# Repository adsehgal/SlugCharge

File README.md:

# *SlugCharge*

SlugCharge was a student run project geared towards helping the homeless communit of Santa Cruz, CA. The project was led by four Electrical Engineering students at the University of California, Santa Cruz. The team aimed towards providing solar powered charging stations to the community so they can stay conencted with family and potential employers that may turn their life around! 

### My Roles

* PCB Design
* Mechnical Design
* Graphic Design
* Video Creation

<!-- START OF PCB SECTION -->
### PCB Design

#### PCB #1 - Testbench V1.0
[Project Files](https://github.com/adsehgal/SlugCharge/tree/master/SlugCharge_Testbench_V1.0) - KiCad
* We first started with making a testbench that was able to run our code and interact with the required I/O </br>
    Requirements:</br>
    * Utilize the **ATmega2560** as the main processor
    * Be **easliy programmable** for future code updates
    * Contain **visual annunciators** for easy state tracking 
    * Utilize **breakout pins** for off-board I/O control
    * Should **not require off-board voltage regulation**
    * Should be easily **hand assembled**
    * Restricted to a **2-layer PCB**
* The design was started off with referring to the Arduino Mega Development board and adapted to fit the required I/O:

* Next I moved onto laying out the PCB as per the requirements to get the following design:

</p>

#### PCB #2 - Motherboard V2.4
[Project Files](https://github.com/adsehgal/SlugCharge/tree/master/SlugCharge_Motherboard) - KiCad
* We followed the success of the testbench with a custom motherboard </br>
    Requirements:</br>
    * Utilize the **ATmega2560** as the main processor
    * Be **easliy programmable** for future code updates
    * Should **not require off-board voltage regulation**
    * Should **not be directly connected** to the individual lockers
    * Restricted to a **2-layer PCB**

To keep the motherboard physically isolated from the individual lockers, we decided to design a daughterboard for each locker that would connect to the motherboard via IDC cables

* Next I moved onto laying out the PCB as per the requirements to get the following design:

#### PCB #3 - Daughterboard V4.0
[Project Files](https://github.com/adsehgal/SlugCharge/tree/master/SlugCharge_Daughterboard) - KiCad
* We followed the success of the testbench with a custom daughterboard </br>
    Requirements:</br>
    * Connect with the motherboard **using IDC cables**
    * Provide a **voltage regulator per locker** to charge devices
    * Should be **easily replacable**
    * Should **not contain any complex devices**
    * Restricted to a **2-layer PCB**

To charge the devices in each locker, we decided to give each of these PCBs a second voltage regulator PCB for easy servicability. This regulator was chose to be the [TPS62133](https://github.com/adsehgal/SlugCharge/tree/master/TPS62133)

* Next I moved onto laying out the PCB as per the requirements to get the following design:

<!-- END OF PCB SECTION -->

<!--START OF  VOLTAGE REGULATOR -->
### Voltage Regulator selection

<!-- END OF VOLTAGE REGULATOR -->
[Regulator Comparison Sheet](https://github.com/adsehgal/SlugCharge/blob/master/Regulator_selection.pdf) - PDF</br>
[Regulator Design Files](https://github.com/adsehgal/SlugCharge/tree/master/TPS62133) - KiCad
* I decided to use the TPS62133 constant 5.0V switching regulator to charge connected devices. This regulator was selected for the following reasons:  </br>
  * Relatively low cost
  * Extremely high efficiency
  * Very low output ripple
  * On chip enable pin
  * High current capability
  
<!-- START OF MECH SECTION -->
### Mechanical Design
[Mechanical Drafts](https://github.com/adsehgal/SlugCharge/tree/master/Mechanical) - Fusion360
* Given the restrictions due to COVID-19, the team was unable to build the station, however we rendered a 3-D model for any future teams that may be intereste in taking up this project</br>
    Requirements:</br>
    * Be designed to accomodate the **average person height**
    * Hold at least **6 devices simultaneously**
    * Be resistant to **tampering**
    * **Solar Powered**

We drafted the 3-D model and orthographic drawings using Fusion360. This was done to aid future teams who may be interested in continuing this project

To educate the community how to use the station we developed two short instructional videos showing so. These can be downloaded via the following hyperlinks

* [Selecting a locker](https://github.com/adsehgal/SlugCharge/blob/master/Mechanical/Get_Device_Final.avi)
* [Retrieving your device](https://github.com/adsehgal/SlugCharge/blob/master/Mechanical/Select_Locker_FInal.avi)
<!-- END OF MECH SECTION -->

### Final Report
[The final team report can be found here](https://github.com/adsehgal/SlugCharge/blob/master/Final_report.pdf)

## Built With

* [KiCad](https://kicad-pcb.org/) - Used to design schematics and PCB layouts
* [Fusion 360](https://www.autodesk.com/products/fusion-360/overview) - Used to design mechanical drafts
* [Arduino IDE](https://www.arduino.cc/) - Used to code the charging station functionaility
* [Affinity Designer](http://affinity.serif.com/) - Used to design logos and other 2-D graphics
* [VSDC Video Editor](http://www.videosoftdev.com/) - Used to design education videos of the charging station

## Authors

* **Aditya Sehgal** - *Systems Integration lead, PCB Designer, Mechanical Drafter and Graphic Designer* - [AdSehgal](https://github.com/AdSehgal)

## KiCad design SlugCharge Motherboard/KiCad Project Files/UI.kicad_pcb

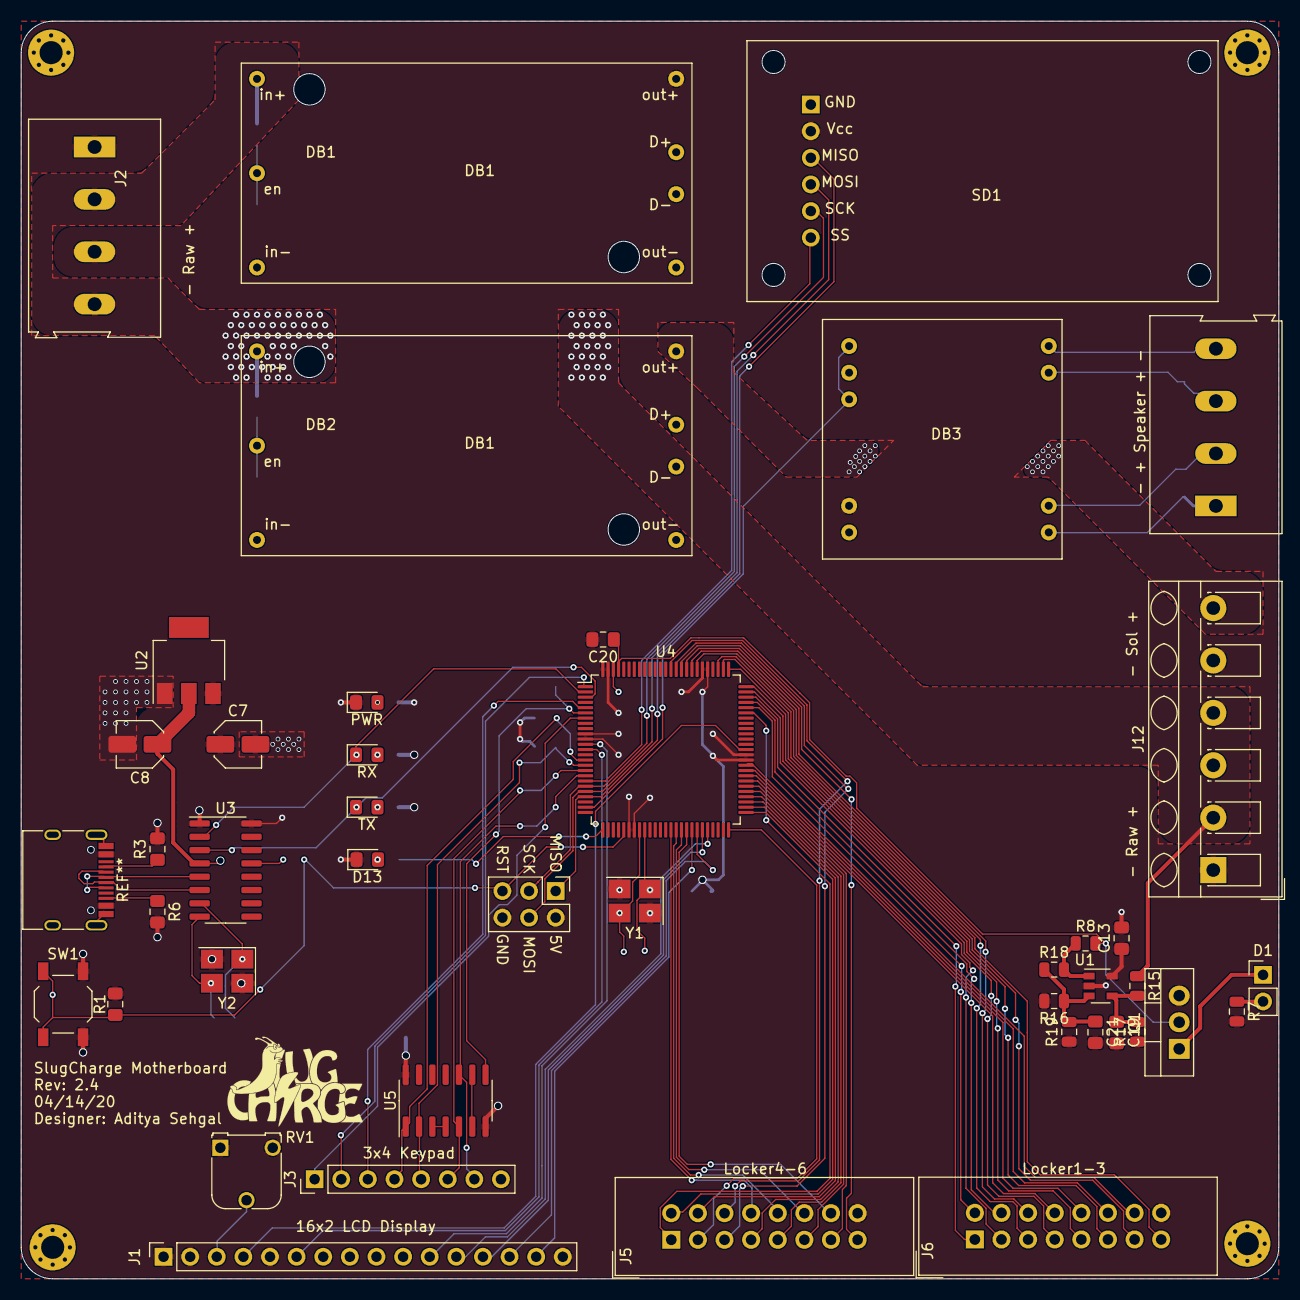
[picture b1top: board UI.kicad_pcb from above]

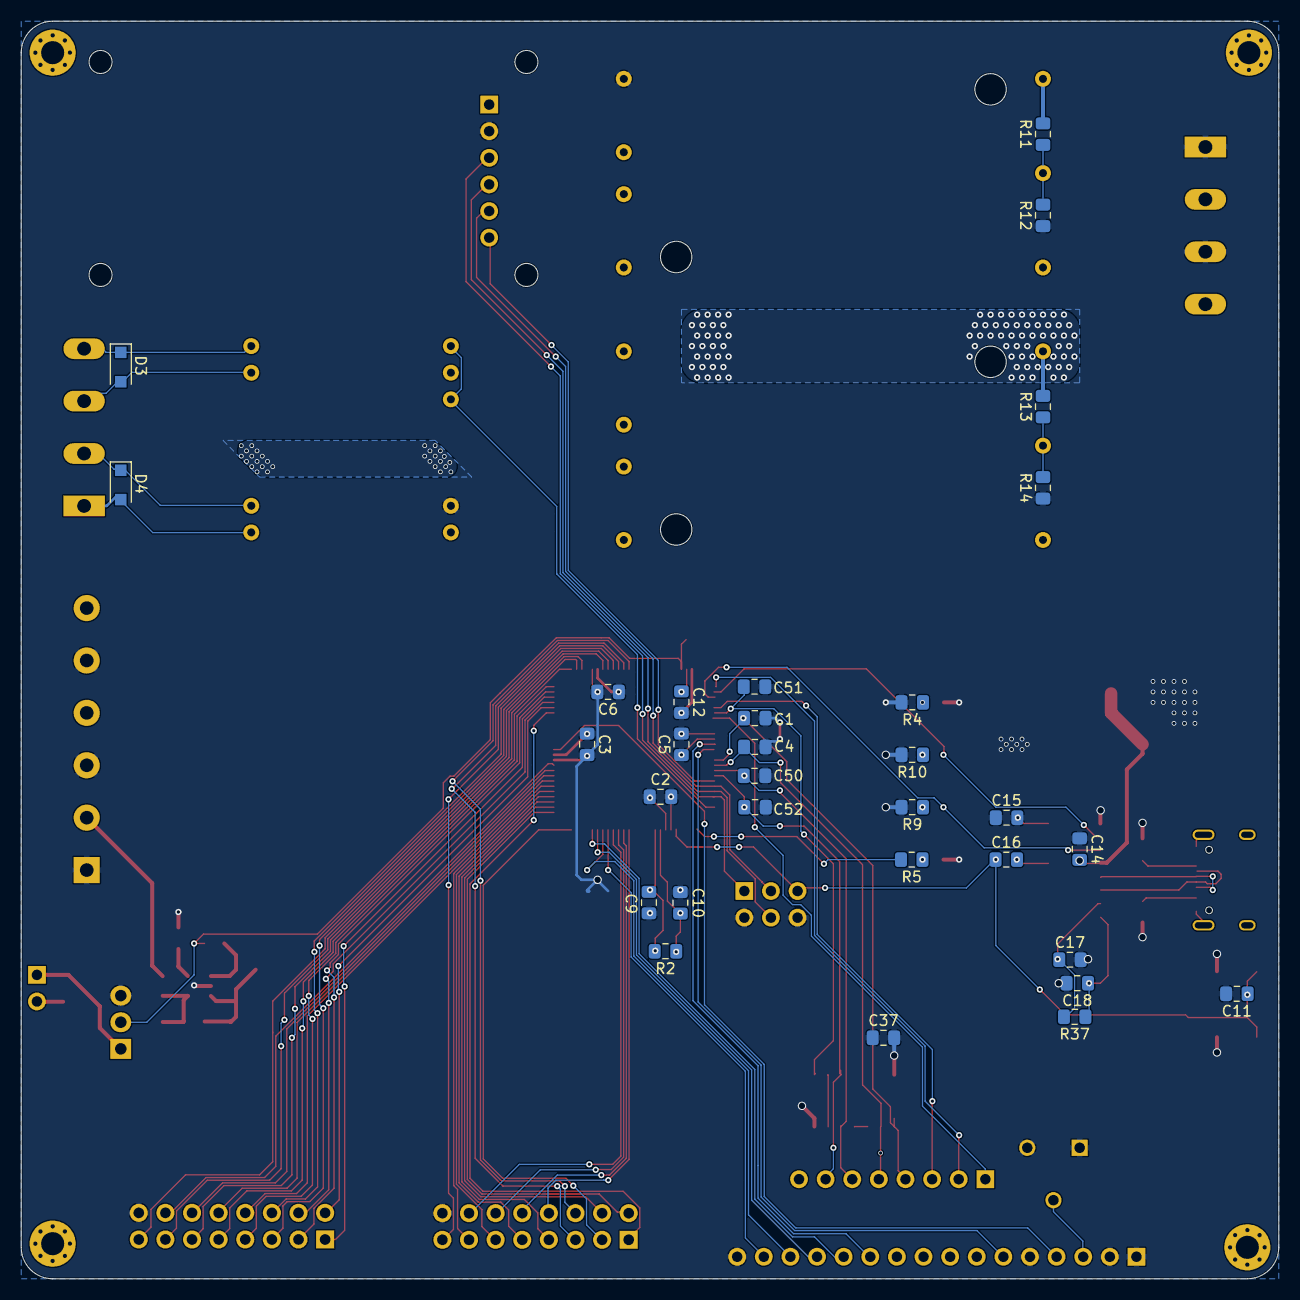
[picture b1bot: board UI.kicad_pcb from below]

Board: 2 copper layers, 120.0 x 120.0 mm, 80 parts (31 on the bottom side), 89 nets.

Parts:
C1, C2, C3, C4, C5, C6, C12, C13, C14, C15, C16, C19, C20, C21, C37, C50, C51, C52: 100nF; C_0805_2012Metric_Pad1.15x1.40mm_HandSolder
C7, C8: 10µF; C_Elec_4x5.4
C9, C10, C11, C17, C18: 22pF; C_0805_2012Metric_Pad1.15x1.40mm_HandSolder
D1: LED_Small; PinHeader_1x02_P2.54mm_Vertical
D3, D4: 1N4004; D_SOD-123F
D13: D13; LED_0805_2012Metric_Pad1.15x1.40mm_HandSolder
DB1: +5V_DB; LM2576_DB
DB2: +12V_DB; LM2576_DB
DB3: PAM8403_DB
H1, H2, H3, H4: MountingHole; MountingHole_2.2mm_M2_Pad_Via
J1: 16x2 LCD Display; PinSocket_1x16_P2.54mm_Vertical
J2: RAW in; TerminalBlock_Altech_AK300-4_P5.00mm
J3: 3x4 Keypad; PinHeader_1x08_P2.54mm_Vertical
J4: ICSP; PinHeader_2x03_P2.54mm_Vertical
J5: Locker4-6; IDC-Header_2x08_P2.54mm_Vertical
J6: Locker1-3; IDC-Header_2x08_P2.54mm_Vertical
J10: Speaker; TerminalBlock_Altech_AK300-4_P5.00mm
J12: Power; TerminalBlock_RND_205-00060_1x06_P5.00mm_45Degree
P1: USB_C_Plug; USB_C_SMD
PWR1: PWR; LED_0805_2012Metric_Pad1.15x1.40mm_HandSolder
Q1: IRF520; TO-220-3_Vertical
R1: 10KΩ; R_0805_2012Metric_Pad1.15x1.40mm_HandSolder
R2, R37: 1MΩ; R_0805_2012Metric_Pad1.15x1.40mm_HandSolder
R3, R6: 5K1; R_0805_2012Metric_Pad1.15x1.40mm_HandSolder
R4, R5, R9, R10: 330Ω; R_0805_2012Metric_Pad1.15x1.40mm_HandSolder
R7: 510R; R_0805_2012Metric
R8: 10K; R_0805_2012Metric
R11, R12, R13, R14: 0Ω; R_0805_2012Metric_Pad1.15x1.40mm_HandSolder
R15: 300K; R_0805_2012Metric
R16: 20K; R_0805_2012Metric
R17: 100K; R_0805_2012Metric
R18: 400K; R_0805_2012Metric
R19: 32.4K; R_0805_2012Metric
RV1: Cntrst Cntrl; Potentiometer_Runtron_RM-065_Vertical
RX1: RX; LED_0805_2012Metric_Pad1.15x1.40mm_HandSolder
SD1: microSD_Adapter; Micro_SD_Module
SW1: RST; SW_SPST_TL3342
TP1: TestPoint; logoinv
TX1: TX; LED_0805_2012Metric_Pad1.15x1.40mm_HandSolder
U1: TLV3201; SOT-23-5
U2: ams1117-3.3V; SOT-223
U3: CH340G; SOIC-16_3.9x9.9mm_P1.27mm
U4: ATmega2560-16AU; TQFP-100_14x14mm_P0.5mm
U5: 74HC08; SOIC-14_3.9x8.7mm_P1.27mm
Y1: 16MHz; Crystal_SMD_3225-4Pin_3.2x2.5mm_HandSoldering
Y2: 12MHz; Crystal_SMD_3225-4Pin_3.2x2.5mm_HandSoldering

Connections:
+3V3: C8.1, C14.2, U2.2 (VO), U3.4 (V3)
+5V: C1.2, C2.1, C2.2, C3.1, C3.2, C4.2, C5.1, C5.2, C6.1, C6.2, C7.1, C7.2, C8.2, C9.2, C10.2, C11.2, C12.2, C13.1, C13.2, C14.1, C15.1, C15.2, C17.2, C18.2, C19.2, C20.2, C21.2, C37.1, C37.2, C50.2, C51.2, C52.2, D13.1 (K), DB1.3 (out+), DB3.4 (Vcc), J1.1, J1.2, J1.5, J1.16, J2.1, J2.3, J4.2, J4.6, J5.16, J6.16, J12.1, J12.3, J12.5, P1.A4 (VBUS), P1.A9 (VBUS), P1.B4 (VBUS), P1.B9 (VBUS), PWR1.1 (K), Q1.3 (S), R1.2, R3.2, R4.2, R6.2, R7.2, R9.2, R10.2, R12.1, R14.1, R16.2, R17.1, R19.1, RV1.1, RV1.3, SD1.2 (Vcc), SW1.2, U1.2 (V-), U1.5 (V+), U2.1 (GND), U2.3 (VI), U3.1 (GND), U3.16 (VCC), U4.10 (VCC), U4.11 (GND), U4.31 (VCC), U4.32 (GND), U4.61 (VCC), U4.62 (GND), U4.80 (VCC), U4.81 (GND), U4.99 (GND), U4.100 (AVCC), U5.7 (GND), U5.14 (VCC), Y1.2, Y1.4, Y2.2, Y2.4
+12V: DB2.3 (out+), J12.6
+BATT: J2.2, J2.4, J12.2, J12.4, R11.2, R13.2, R15.1
+VSW: DB1.1 (in+), DB2.1 (in+)
/A10: J5.6, U4.87 (PK2)
/A11: J5.5, U4.86 (PK3)
/A12: J5.15, U4.85 (PK4)
/A13: J6.6, U4.84 (PK5)
/A14: J6.5, U4.83 (PK6)
/A15: J6.15, U4.82 (PK7)
/AREF: C12.1, U4.98 (AREF)
/BLI: C20.1, Q1.2 (G), R8.2, U4.97 (PF0)
/D2: C51.1, U4.6 (PE4), U5.8
/D3: J3.1, U4.7 (PE5)
/D4: J3.2, U4.1 (PG5)
/D5: J3.3, U4.5 (PE3)
/D6: C1.1, J3.4, U4.15 (PH3), U5.1
/D7: C4.1, J3.5, U4.16 (PH4), U5.2
/D8: C50.1, J3.6, U4.17 (PH5), U5.5
/D9: C52.1, J3.7, U4.18 (PH6), U5.10
/D11: DB3.1 (Lin), DB3.3 (Rin), U4.24 (PB5)
/D15: J1.4, U4.63 (PJ0)
/D16: J1.6, U4.13 (PH1)
/D17: J1.11, U4.12 (PH0)
/D18: J1.12, U4.46 (PD3)
/D19: J1.13, U4.45 (PD2)
/D20: J1.14, U4.44 (PD1)
/D21: J1.15, U4.43 (PD0)
/D22: J6.13, U4.78 (PA0)
/D23: J6.11, U4.77 (PA1)
/D24: J6.9, U4.76 (PA2)
/D25: J6.7, U4.75 (PA3)
/D26: J6.3, U4.74 (PA4)
/D27: J6.1, U4.73 (PA5)
/D28: J6.4, U4.72 (PA6)
/D29: J6.2, U4.71 (PA7)
/D30: J6.14, U4.60 (PC7)
/D31: J6.12, U4.59 (PC6)
/D32: J6.10, U4.58 (PC5)
/D33: J6.8, U4.57 (PC4)
/D34: J5.13, U4.56 (PC3)
/D35: J5.11, U4.55 (PC2)
/D36: J5.9, U4.54 (PC1)
/D37: J5.7, U4.53 (PC0)
/D38: J5.3, U4.50 (PD7)
/D39: J5.1, U4.70 (PG2)
/D40: J5.4, U4.52 (PG1)
/D41: J5.2, U4.51 (PG0)
/D42: J5.14, U4.42 (PL7)
/D43: J5.12, U4.41 (PL6)
/D44: J5.10, U4.40 (PL5)
/D45: J5.8, U4.39 (PL4)
/D50_MISO: J4.1, SD1.3 (MISO), U4.22 (PB3)
/D51_MOSI: J4.4, SD1.4 (MOSI), U4.21 (PB2)
/D52_SCK: J4.3, SD1.5 (SCK), U4.20 (PB1)
/D53_SS: SD1.6 (SS), U4.19 (PB0)
/D+: P1.A6 (D+), P1.B6 (D+)
/D-: P1.A7 (D-), P1.B7 (D-)
/OSC1: C9.1, R2.2, U4.34 (XTAL1), Y1.1
/OSC2: C10.1, R2.1, U4.33 (XTAL2), Y1.3
/RST: C11.1, C16.1, J4.5, R1.1, SW1.1, U4.30 (~RESET)
/RX: RX1.1 (K), U3.2 (TXD), U4.2 (PE0)
/TX: TX1.1 (K), U3.3 (RXD), U4.3 (PE1)
GNDREF: DB1.2 (in-), DB1.4 (out-), DB2.2 (in-), DB2.4 (out-), DB3.2 (CMN), DB3.5 (GND), P1.A1 (GND), P1.A12 (GND), P1.B1 (GND), P1.B12 (GND), P1.S1 (SHIELD), SD1.1 (GND)
unnamed: C16.2, U3.13 (~DTR)
unnamed: C17.1, R37.2, U3.7 (XI), Y2.1
unnamed: C18.1, R37.1, U3.8 (XO), Y2.3
unnamed: C19.1, R15.2, R17.2, U1.4 (-)
unnamed: C21.1, R16.1, R18.1, R19.2, U1.3 (+)
unnamed: D1.1 (K), Q1.1 (D)
unnamed: D1.2 (A), R7.1
unnamed: D3.1 (K), DB3.6 (Rout-), J10.4
unnamed: D3.2 (A), DB3.7 (Rout+), J10.3
unnamed: D4.1 (K), DB3.8 (Lout+), J10.2
unnamed: D4.2 (A), DB3.9 (Lout-), J10.1
unnamed: D13.2 (A), R5.1
unnamed: DB1.5 (en), R11.1, R12.2
unnamed: DB2.5 (en), R13.1, R14.2
unnamed: J1.3, RV1.2
unnamed: P1.A5 (CC1), R3.1
unnamed: P1.B5 (CC2), R6.1
unnamed: PWR1.2 (A), R4.1
unnamed: R5.2, U4.26 (PB7)
unnamed: R9.1, TX1.2 (A)
unnamed: R10.1, RX1.2 (A)
unnamed: R8.1, R18.2, U1.1 (out)
unnamed: U5.3, U5.4
unnamed: U5.6, U5.9

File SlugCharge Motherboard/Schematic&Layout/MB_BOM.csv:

"Id";"Designator";"Package";"Quantity";"Designation";"Supplier and ref";
1;"RV1";"Potentiometer_Runtron_RM-065_Vertical";1;"Cntrst Cntrl";;;
2;"U5";"SOIC-14_3.9x8.7mm_P1.27mm";1;"74HC08";;;
3;"J5";"IDC-Header_2x08_P2.54mm_Vertical";1;"Locker4-6";;;
4;"J6";"IDC-Header_2x08_P2.54mm_Vertical";1;"Locker1-3";;;
5;"J12";"TerminalBlock_RND_205-00060_1x06_P5.00mm_45Degree";1;" ";;;
6;"J10";"TerminalBlock_Altech_AK300-4_P5.00mm";1;"Speaker";;;
7;"J2";"TerminalBlock_Altech_AK300-4_P5.00mm";1;"RAW in";;;
8;"P1";"USB_C_SMD";1;"USB_C_Plug";;;
9;"DB3";"PAM8403_DB";1;"PAM8403_DB";;;
10;"SD1";"Micro_SD_Module";1;"microSD_Adapter";;;
11;"DB2";"LM2576_DB";1;"+12V_DB";;;
12;"DB1";"LM2576_DB";1;"+5V_DB";;;
13;"U4";"TQFP-100_14x14mm_P0.5mm";1;"ATmega2560-16AU";;;
14;"R14,R13,R12,R11";"R_0805_2012Metric_Pad1.15x1.40mm_HandSolder";4;"0Ω";;;
15;"U2";"SOT-223";1;"ams1117-3.3V";;;
16;"Y2";"Crystal_SMD_3225-4Pin_3.2x2.5mm_HandSoldering";1;"12MHz";;;
17;"Y1";"Crystal_SMD_3225-4Pin_3.2x2.5mm_HandSoldering";1;"16MHz";;;
18;"U3";"SOIC-16_3.9x9.9mm_P1.27mm";1;"CH340G";;;
19;"TX1";"LED_0805_2012Metric_Pad1.15x1.40mm_HandSolder";1;"TX";;;
20;"SW1";"SW_SPST_TL3342";1;"RST";;;
21;"RX1";"LED_0805_2012Metric_Pad1.15x1.40mm_HandSolder";1;"RX";;;
22;"R37,R2";"R_0805_2012Metric_Pad1.15x1.40mm_HandSolder";2;"1MΩ";;;
23;"R10,R9,R5,R4";"R_0805_2012Metric_Pad1.15x1.40mm_HandSolder";4;"330Ω";;;
24;"R6,R3";"R_0805_2012Metric_Pad1.15x1.40mm_HandSolder";2;"5K1";;;
25;"R1";"R_0805_2012Metric_Pad1.15x1.40mm_HandSolder";1;"1KΩ";;;
26;"PWR1";"LED_0805_2012Metric_Pad1.15x1.40mm_HandSolder";1;"PWR";;;
27;"J4";"PinHeader_2x03_P2.54mm_Vertical";1;"Conn_02x03_Odd_Even";;;
28;"J3";"PinHeader_1x08_P2.54mm_Vertical";1;"3x4 Keypad";;;
29;"J1";"PinSocket_1x16_P2.54mm_Vertical";1;"16x2 LCD Display";;;
30;"H4,H3,H2,H1";"MountingHole_2.2mm_M2_Pad_Via";4;"MountingHole";;;
31;"D13";"LED_0805_2012Metric_Pad1.15x1.40mm_HandSolder";1;"D13";;;
32;"D4,D3";"D_SOD-123F";2;"D_Schottky";;;
33;"C52,C51,C50,C37,C16,C15,C14,C12,C6,C5,C4,C3,C2,C1";"C_0805_2012Metric_Pad1.15x1.40mm_HandSolder";14;"100nF";;;
34;"C18,C17,C11,C10,C9";"C_0805_2012Metric_Pad1.15x1.40mm_HandSolder";5;"22pF";;;
35;"C8,C7";"C_Elec_4x5.4";2;"10µF";;;
36;"TP1";"logoinv";1;"TestPoint";;;

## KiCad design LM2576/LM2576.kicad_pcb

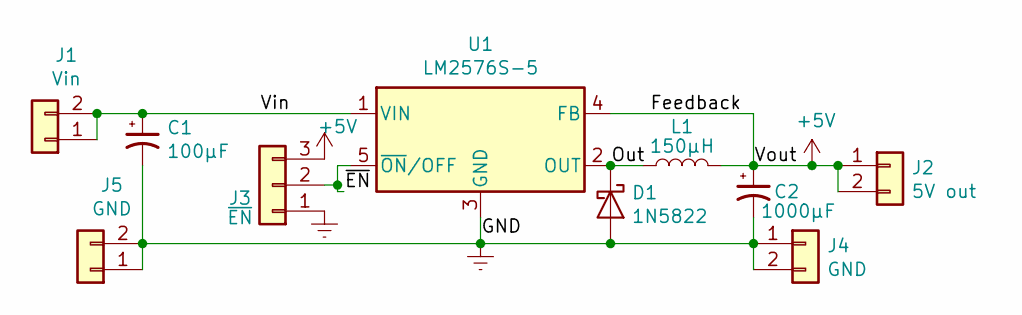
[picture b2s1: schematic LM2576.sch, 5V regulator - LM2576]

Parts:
C1: 100µF; C_Elec_8x10.2
C2: 1000µF; C_Elec_10x10.2
D1: 1N5822; D_DO-201AD_P15.24mm_Horizontal
J1: Vin; PinHeader_1x02_P2.54mm_Vertical
J2: 5V out; PinHeader_1x02_P2.54mm_Vertical
J3: ~EN; PinHeader_1x03_P2.54mm_Vertical
J4, J5: GND; PinHeader_1x02_P2.54mm_Vertical
L1: 150µH; L_Radial_D14.2mm_P10.00mm_Neosid_SD14
U1: LM2576S-5; TO-263-5_TabPin3

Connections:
+5V: C2.1, J2.1, J2.2, J3.3, L1.2, U1.4 (FB)
/Out: D1.1 (K), L1.1, U1.2 (OUT)
/Vin: C1.1, J1.1, J1.2, U1.1 (VIN)
/~EN: J3.2, U1.5 (~ON~/OFF)
GNDREF: C1.2, C2.2, D1.2 (A), J3.1, J4.1, J4.2, J5.1, J5.2, U1.3 (GND)

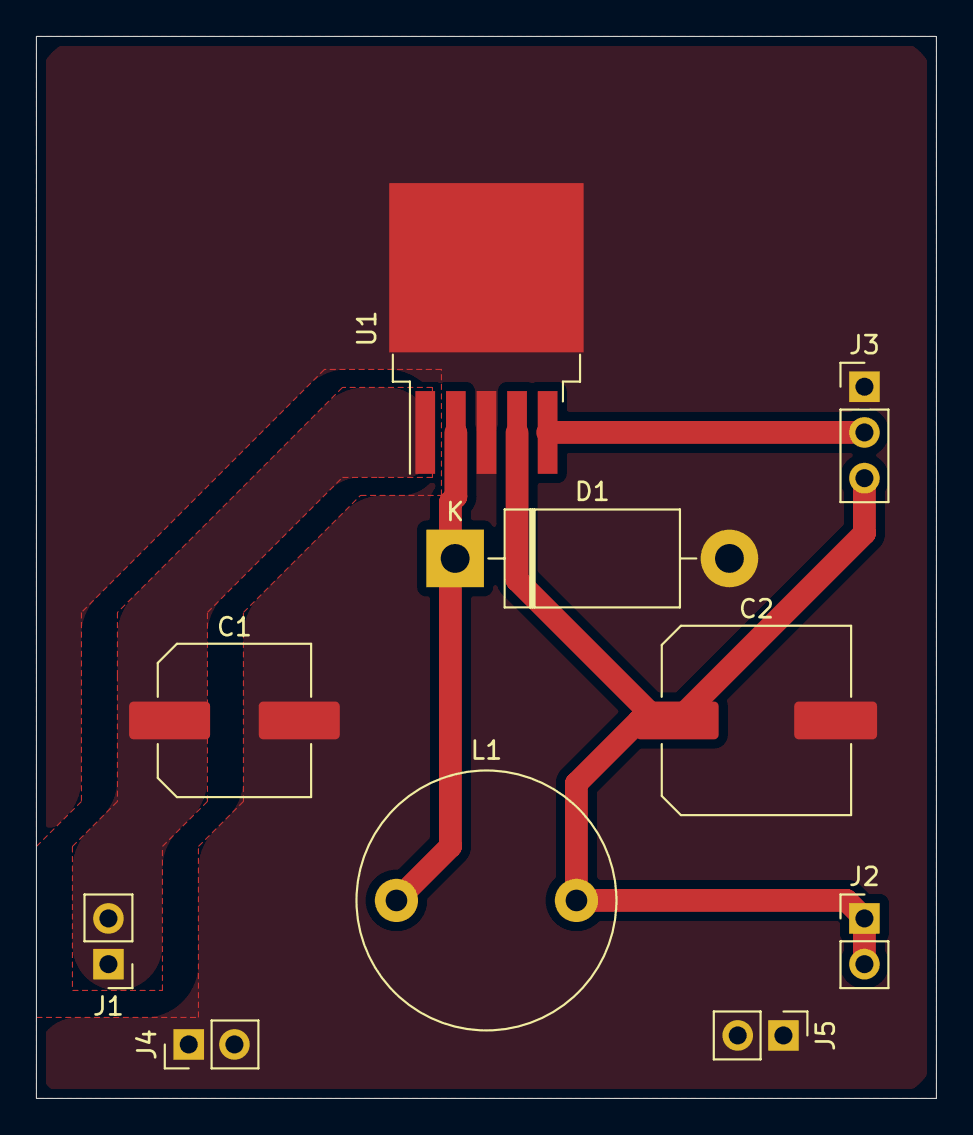
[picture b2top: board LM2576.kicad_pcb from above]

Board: 2 copper layers, 50.0 x 59.0 mm, 10 parts (0 on the bottom side), 5 nets.

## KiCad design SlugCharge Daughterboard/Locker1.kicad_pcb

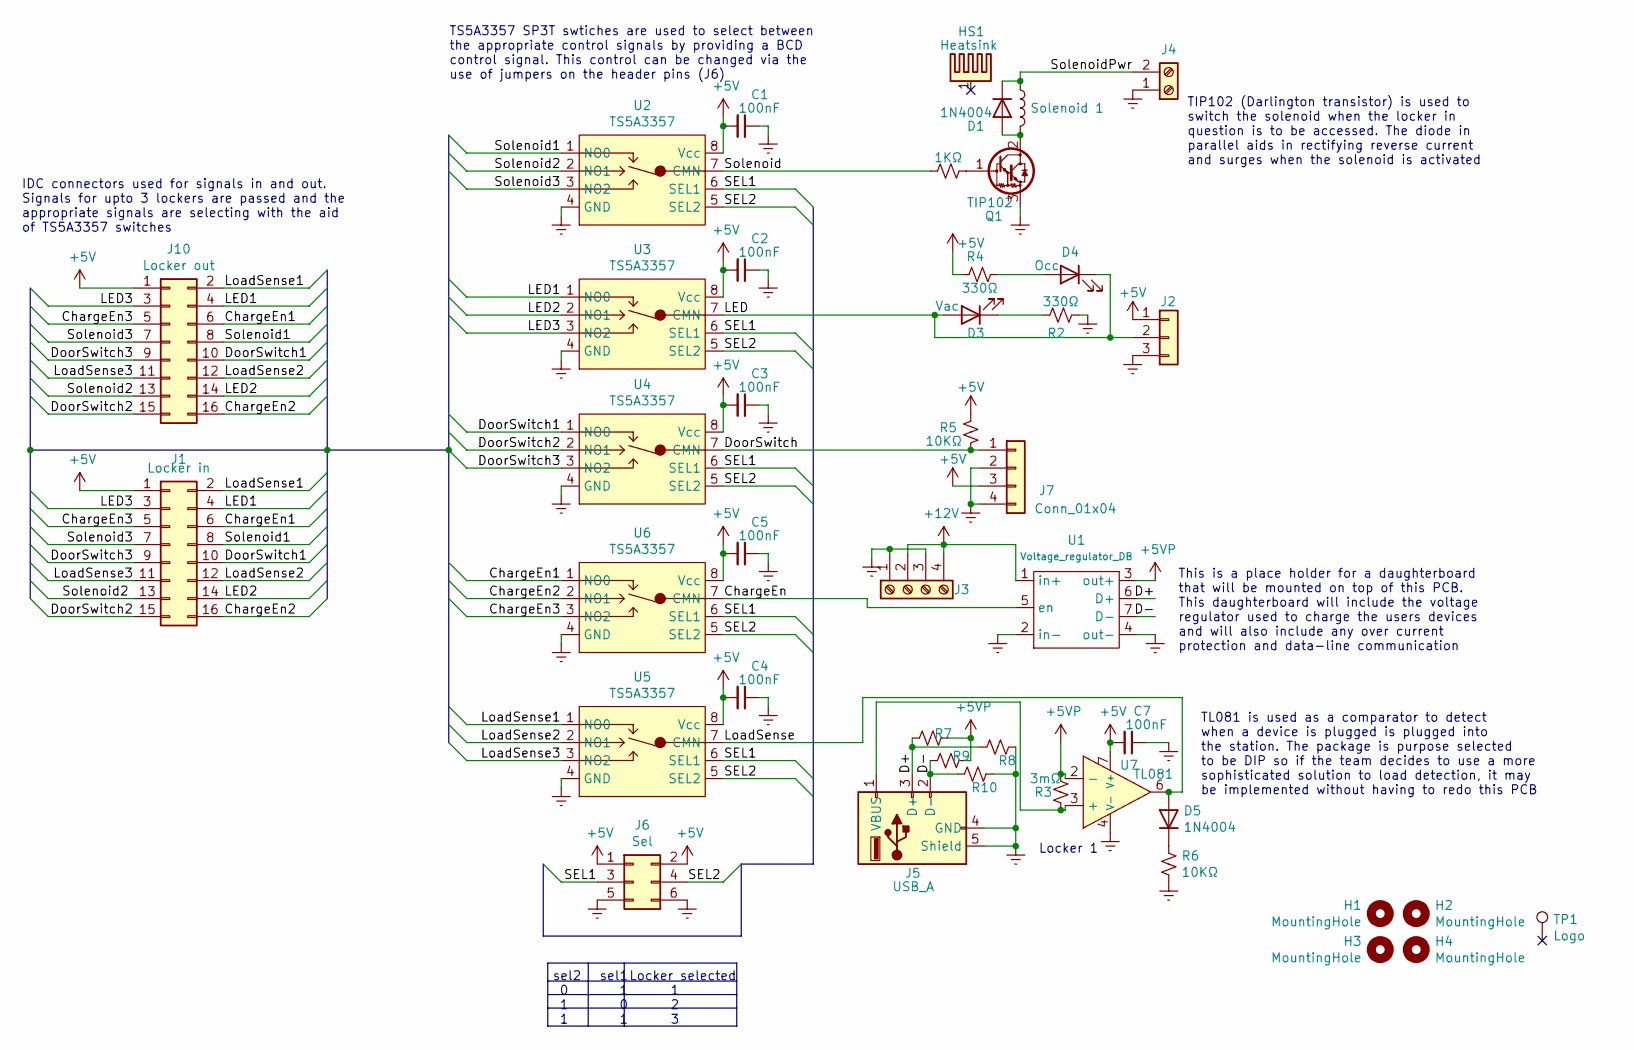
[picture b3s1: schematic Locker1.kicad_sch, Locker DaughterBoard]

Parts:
C1, C2, C3, C4, C5, C7: 100nF; C_0805_2012Metric_Pad1.15x1.40mm_HandSolder
D1, D5: 1N4004; D_SOD-123F
D3: Vac; LED_1206_3216Metric_Pad1.42x1.75mm_HandSolder
D4: Occ; LED_1206_3216Metric_Pad1.42x1.75mm_HandSolder
H1, H2, H3, H4: MountingHole; MountingHole_2.2mm_M2_Pad_Via
HS1: Heatsink; TO-220_Vertical_XSD_C116600
J1: Locker in; IDC-Header_2x08_P2.54mm_Vertical
J2: Conn_01x04; PinHeader_1x03_P2.54mm_Vertical
J3: Unreg 12V - charge; TerminalBlock_Altech_AK300-4_P5.00mm
J4: Solenoid Power; TerminalBlock_Altech_AK300-2_P5.00mm
J5: USB_A; USB_A_Stewart_SS-52100-001_Horizontal
J6: Sel; PinHeader_2x03_P2.54mm_Vertical
J7: Conn_01x04; PinHeader_2x02_P2.54mm_Vertical
J10: Locker out; IDC-Header_2x08_P2.54mm_Vertical
L1: Solenoid 1; TerminalBlock_Altech_AK300-2_P5.00mm
Q1: TIP102; TO-220-3_Vertical
R1: 1KΩ; R_0805_2012Metric_Pad1.15x1.40mm_HandSolder
R2, R4: 330Ω; R_0805_2012Metric_Pad1.15x1.40mm_HandSolder
R3: 3mΩ; R_0805_2012Metric_Pad1.15x1.40mm_HandSolder
R5, R6, R7, R8, R9, R10: 10KΩ; R_0805_2012Metric_Pad1.15x1.40mm_HandSolder
TP1: Logo; logoinv
U1: Voltage_regulator_DB; LM2576_DB
U2, U3, U4, U5, U6: TS5A3357; VSSOP-8_2.4x2.1mm_P0.5mm
U7: TL081; DIP-8_W7.62mm

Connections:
+5V: C1.2, C2.2, C3.2, C4.2, C5.2, C7.2, J1.1, J2.1, J6.1, J6.2, J7.3, J10.1, R4.2, R5.2, U2.8 (Vcc), U3.8 (Vcc), U4.8 (Vcc), U5.8 (Vcc), U6.8 (Vcc), U7.7 (V+)
+5VP: R3.1, R7.2, R9.2, U1.3 (out+), U7.2 (-)
+12V: J3.2, J3.4, U1.1 (in+)
/ChargeEn: U1.5 (en), U6.7 (CMN)
/ChargeEn1: J1.6, J10.6, U6.1 (NO0)
/ChargeEn2: J1.16, J10.16, U6.2 (NO1)
/ChargeEn3: J1.5, J10.5, U6.3 (NO2)
/D+: J5.3 (D+), R7.1, R8.2, U1.6 (D+)
/D-: J5.2 (D-), R9.1, R10.2, U1.7 (D-)
/DoorSwitch: J7.1, R5.1, U4.7 (CMN)
/DoorSwitch1: J1.10, J10.10, U4.1 (NO0)
/DoorSwitch2: J1.15, J10.15, U4.2 (NO1)
/DoorSwitch3: J1.9, J10.9, U4.3 (NO2)
/LED: D3.2 (A), D4.1 (K), J2.2, U3.7 (CMN)
/LED1: J1.4, J10.4, U3.1 (NO0)
/LED2: J1.14, J10.14, U3.2 (NO1)
/LED3: J1.3, J10.3, U3.3 (NO2)
/LoadSense: D5.2 (A), U5.7 (CMN), U7.6
/LoadSense1: J1.2, J10.2, U5.1 (NO0)
/LoadSense2: J1.12, J10.12, U5.2 (NO1)
/LoadSense3: J1.11, J10.11, U5.3 (NO2)
/SEL1: J6.3, U2.6 (SEL1), U3.6 (SEL1), U4.6 (SEL1), U5.6 (SEL1), U6.6 (SEL1)
/SEL2: J6.4, U2.5 (SEL2), U3.5 (SEL2), U4.5 (SEL2), U5.5 (SEL2), U6.5 (SEL2)
/Solenoid: R1.1, U2.7 (CMN)
/Solenoid1: J1.8, J10.8, U2.1 (NO0)
/Solenoid2: J1.13, J10.13, U2.2 (NO1)
/Solenoid3: J1.7, J10.7, U2.3 (NO2)
/SolenoidPwr: D1.1 (K), J4.2, L1.1
GNDREF: C1.1, C2.1, C3.1, C4.1, C5.1, C7.1, J2.3, J3.1, J3.3, J4.1, J5.4 (GND), J5.5 (Shield), J6.5, J6.6, J7.2, J7.4, Q1.3 (E), R2.2, R6.2, R8.1, R10.1, U1.2 (in-), U1.4 (out-), U2.4 (GND), U3.4 (GND), U4.4 (GND), U5.4 (GND), U6.4 (GND), U7.4 (V-)
unnamed: D1.2 (A), L1.2, Q1.2 (C)
unnamed: D3.1 (K), R2.1
unnamed: D4.2 (A), R4.1
unnamed: D5.1 (K), R6.1
unnamed: J5.1 (VBUS), R3.2, U7.3 (+)
unnamed: Q1.1 (B), R1.2

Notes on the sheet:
IDC connectors used for signals in and out. Signals for upto 3 lockers are passed and the appropriate signals are selecting with the aid of TS5A3357 switches
TS5A3357 SP3T swtiches are used to select between the appropriate control signals by providing a BCD control signal. This control can be changed via the use of jumpers on the header pins (J6)
sel2 0 1 1
Locker selected 1 2 3
sel1 1 0 1
Locker 1
This is a place holder for a daughterboard that will be mounted on top of this PCB. This daughterboard will include the voltage regulator used to charge the users devices and will also include any over current protection and data-line communication
TIP102 (Darlington transistor) is used to switch the solenoid when the locker in question is to be accessed. The diode in parallel aids in rectifying reverse current and surges when the solenoid is activated
TL081 is used as a comparator to detect when a device is plugged is plugged into the station. The package is purpose selected to be DIP so if the team decides to use a more sophisticated solution to load detection, it may be implemented without having to redo this PCB

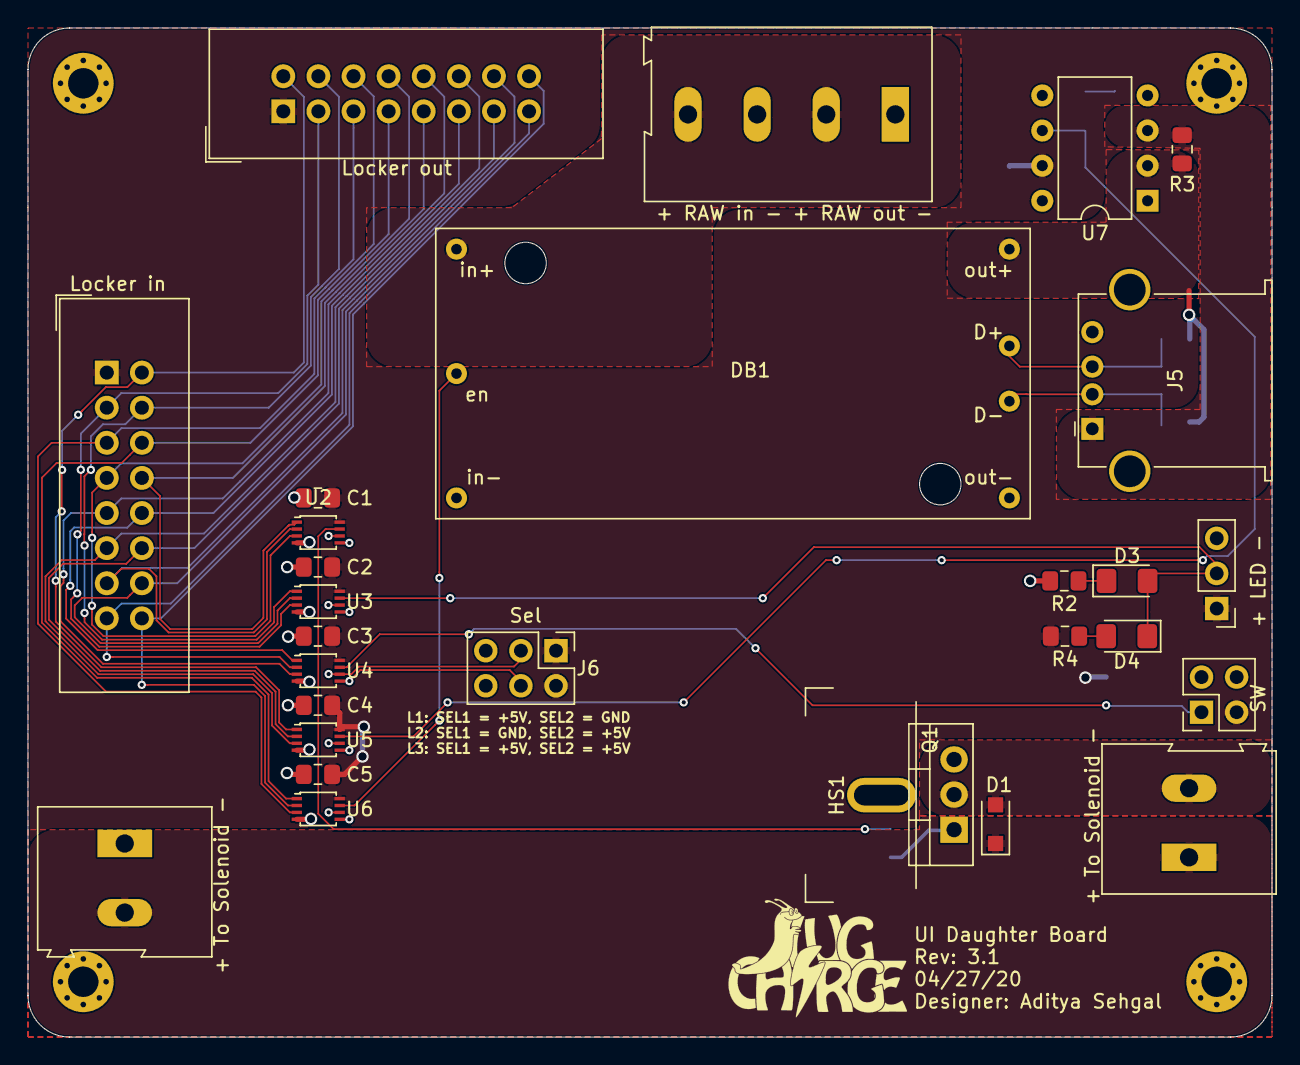
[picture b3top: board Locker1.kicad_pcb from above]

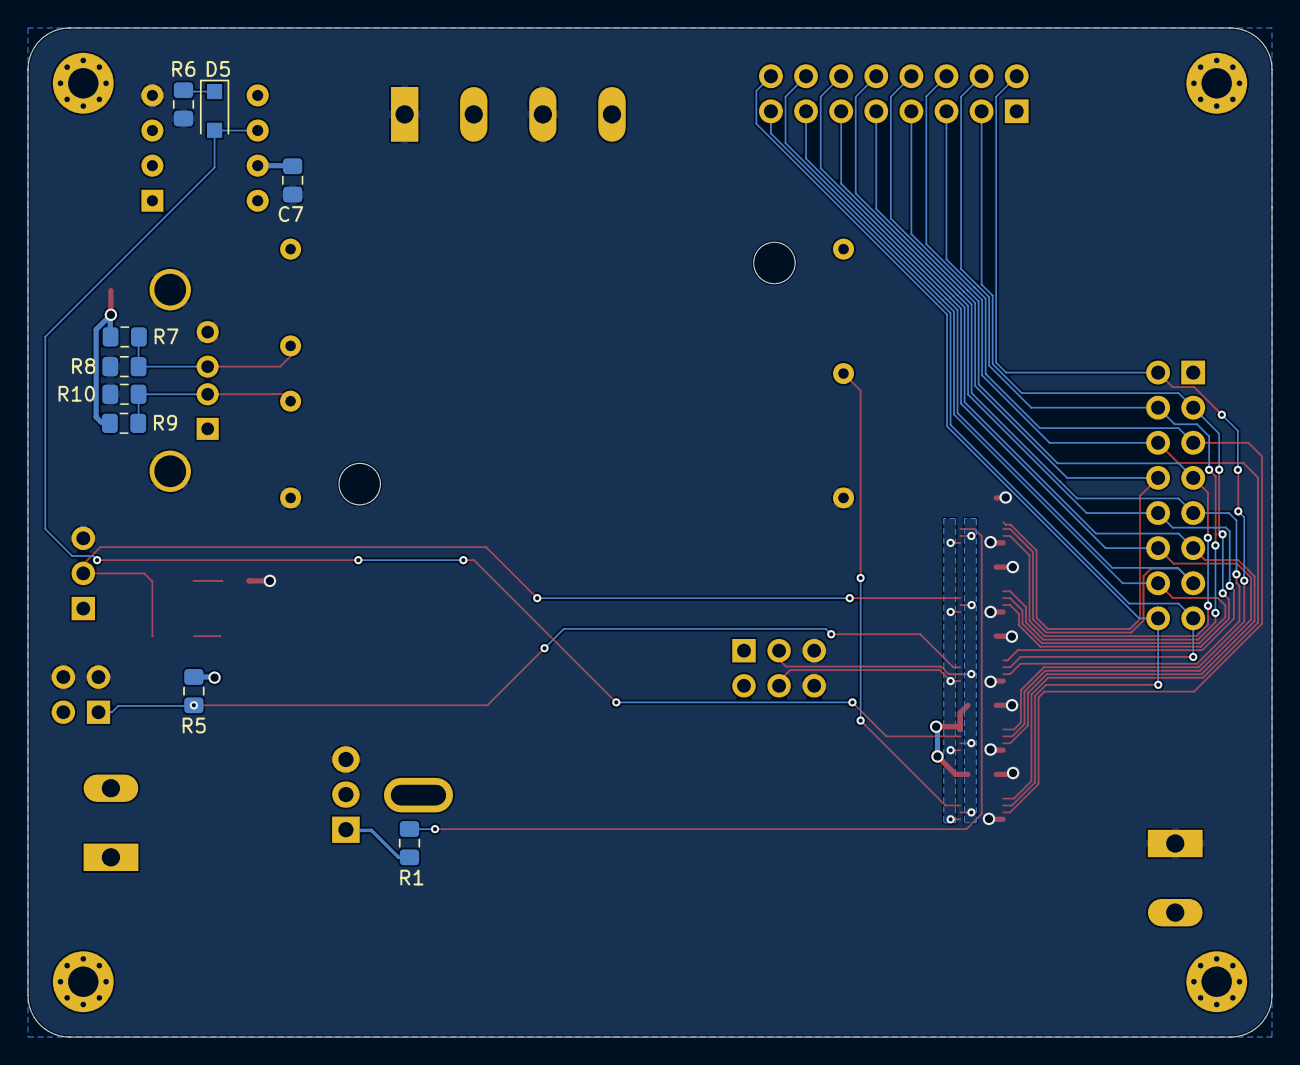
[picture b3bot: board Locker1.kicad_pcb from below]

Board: 2 copper layers, 90.0 x 73.0 mm, 43 parts (9 on the bottom side), 35 nets.

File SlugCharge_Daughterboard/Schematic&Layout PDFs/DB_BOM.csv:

"Id";"Designator";"Package";"Quantity";"Designation";"Supplier and ref";
1;"J6";"PinHeader_2x03_P2.54mm_Vertical";1;"Sel";;;
2;"U7";"DIP-8_W7.62mm";1;"TL081";;;
3;"U1";"LM2576_DB";1;"LM2576_DB";;;
4;"U2,U6,U5,U4,U3";"VSSOP-8_2.4x2.1mm_P0.5mm";5;"TS5A3357";;;
5;"C5,C4,C3,C2,C1,C7";"C_0805_2012Metric_Pad1.15x1.40mm_HandSolder";6;"100nF";;;
6;"HS1";"TO-220_Heatsink";1;"Heatsink";;;
7;"J5";"USB_A_Stewart_SS-52100-001_Horizontal";1;"USB_A";;;
8;"J3";"TerminalBlock_Altech_AK300-4_P5.00mm";1;"Unreg 12V - charge";;;
9;"J1";"IDC-Header_2x08_P2.54mm_Vertical";1;"Locker in";;;
10;"J2";"PinHeader_1x03_P2.54mm_Vertical";1;"Conn_01x04";;;
11;"J10";"IDC-Header_2x08_P2.54mm_Vertical";1;"Locker out";;;
12;"L1";"TerminalBlock_Altech_AK300-2_P5.00mm";1;"Solenoid 1";;;
13;"J4";"TerminalBlock_Altech_AK300-2_P5.00mm";1;"Solenoid Power";;;
14;"R1";"R_0805_2012Metric_Pad1.15x1.40mm_HandSolder";1;"1KΩ";;;
15;"R10,R9,R8,R7,R6,R5";"R_0805_2012Metric_Pad1.15x1.40mm_HandSolder";6;"10KΩ";;;
16;"TP1";"logoinv";1;"TestPoint";;;
17;"J7";"PinHeader_2x02_P2.54mm_Vertical";1;"Conn_01x04";;;
18;"D5,D1";"D_SOD-123F";2;"1N4004";;;
19;"H4,H3,H2,H1";"MountingHole_2.2mm_M2_Pad_Via";4;"MountingHole";;;
20;"R4,R2";"R_0805_2012Metric_Pad1.15x1.40mm_HandSolder";2;"330Ω";;;
21;"R3";"R_0805_2012Metric_Pad1.15x1.40mm_HandSolder";1;"3mΩ";;;
22;"Q1";"TO-220-3_Vertical";1;"TIP102";;;
23;"D4";"LED_1206_3216Metric_Pad1.42x1.75mm_HandSolder";1;"Occ";;;
24;"D3";"LED_1206_3216Metric_Pad1.42x1.75mm_HandSolder";1;"Vac";;;

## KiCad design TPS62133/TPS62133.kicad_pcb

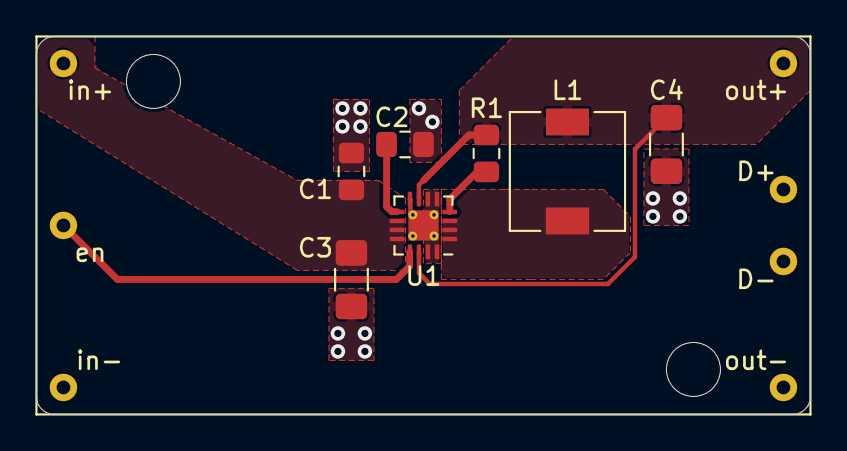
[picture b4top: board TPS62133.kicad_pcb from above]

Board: 2 copper layers, 43.0 x 21.0 mm, 8 parts (0 on the bottom side), 7 nets.

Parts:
C1: 100nF; C_0805_2012Metric_Pad1.15x1.40mm_HandSolder
C2: 620pF; C_0805_2012Metric_Pad1.15x1.40mm_HandSolder
C3: 10µF; C_1206_3216Metric_Pad1.42x1.75mm_HandSolder
C4: 22µF; C_1206_3216Metric_Pad1.42x1.75mm_HandSolder
DB1: DB_42x21; DB_43x21
L1: 2.2µH; L_6.3x6.3_H3
R1: 100K; R_0805_2012Metric_Pad1.15x1.40mm_HandSolder
U1: TPS62133; VQFN-16-1EP_3x3mm_P0.5mm_EP1.68x1.68mm_ThermalVias

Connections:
/+5V: C4.1, DB1.3 (out+), L1.2, R1.2, U1.7 (FSW), U1.14 (VOS)
/EN: DB1.5 (en), U1.13 (en)
/Vin: C1.1, C3.1, DB1.1 (in+), U1.10 (AVin), U1.11 (PVin), U1.12 (PVin)
GNDREF: C1.2, C2.2, C3.2, C4.2, DB1.2 (GND), DB1.4 (GND), U1.5 (FB), U1.6 (AGND), U1.8 (DEF), U1.15 (PGND), U1.16 (PGND), U1.17 (EP)
unnamed: C2.1, U1.9 (SS_TR)
unnamed: L1.1, U1.1 (SW), U1.2 (SW), U1.3 (SW)
unnamed: R1.1, U1.4 (PG)

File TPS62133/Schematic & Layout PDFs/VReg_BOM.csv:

"Id";"Designator";"Package";"Quantity";"Designation";"Supplier and ref";
1;"DB1";"DB_43x21";1;"DB_42x21";;;
2;"C4";"C_1206_3216Metric_Pad1.42x1.75mm_HandSolder";1;"22µF";;;
3;"L1";"L_6.3x6.3_H3";1;"2.2µH";;;
4;"U1";"VQFN-16-1EP_3x3mm_P0.5mm_EP1.68x1.68mm_ThermalVias";1;"TPS62133";;;
5;"R1";"R_0805_2012Metric_Pad1.15x1.40mm_HandSolder";1;"100K";;;
6;"C3";"C_1206_3216Metric_Pad1.42x1.75mm_HandSolder";1;"10µF";;;
7;"C2";"C_0805_2012Metric_Pad1.15x1.40mm_HandSolder";1;"620pF";;;
8;"C1";"C_0805_2012Metric_Pad1.15x1.40mm_HandSolder";1;"100nF";;;
